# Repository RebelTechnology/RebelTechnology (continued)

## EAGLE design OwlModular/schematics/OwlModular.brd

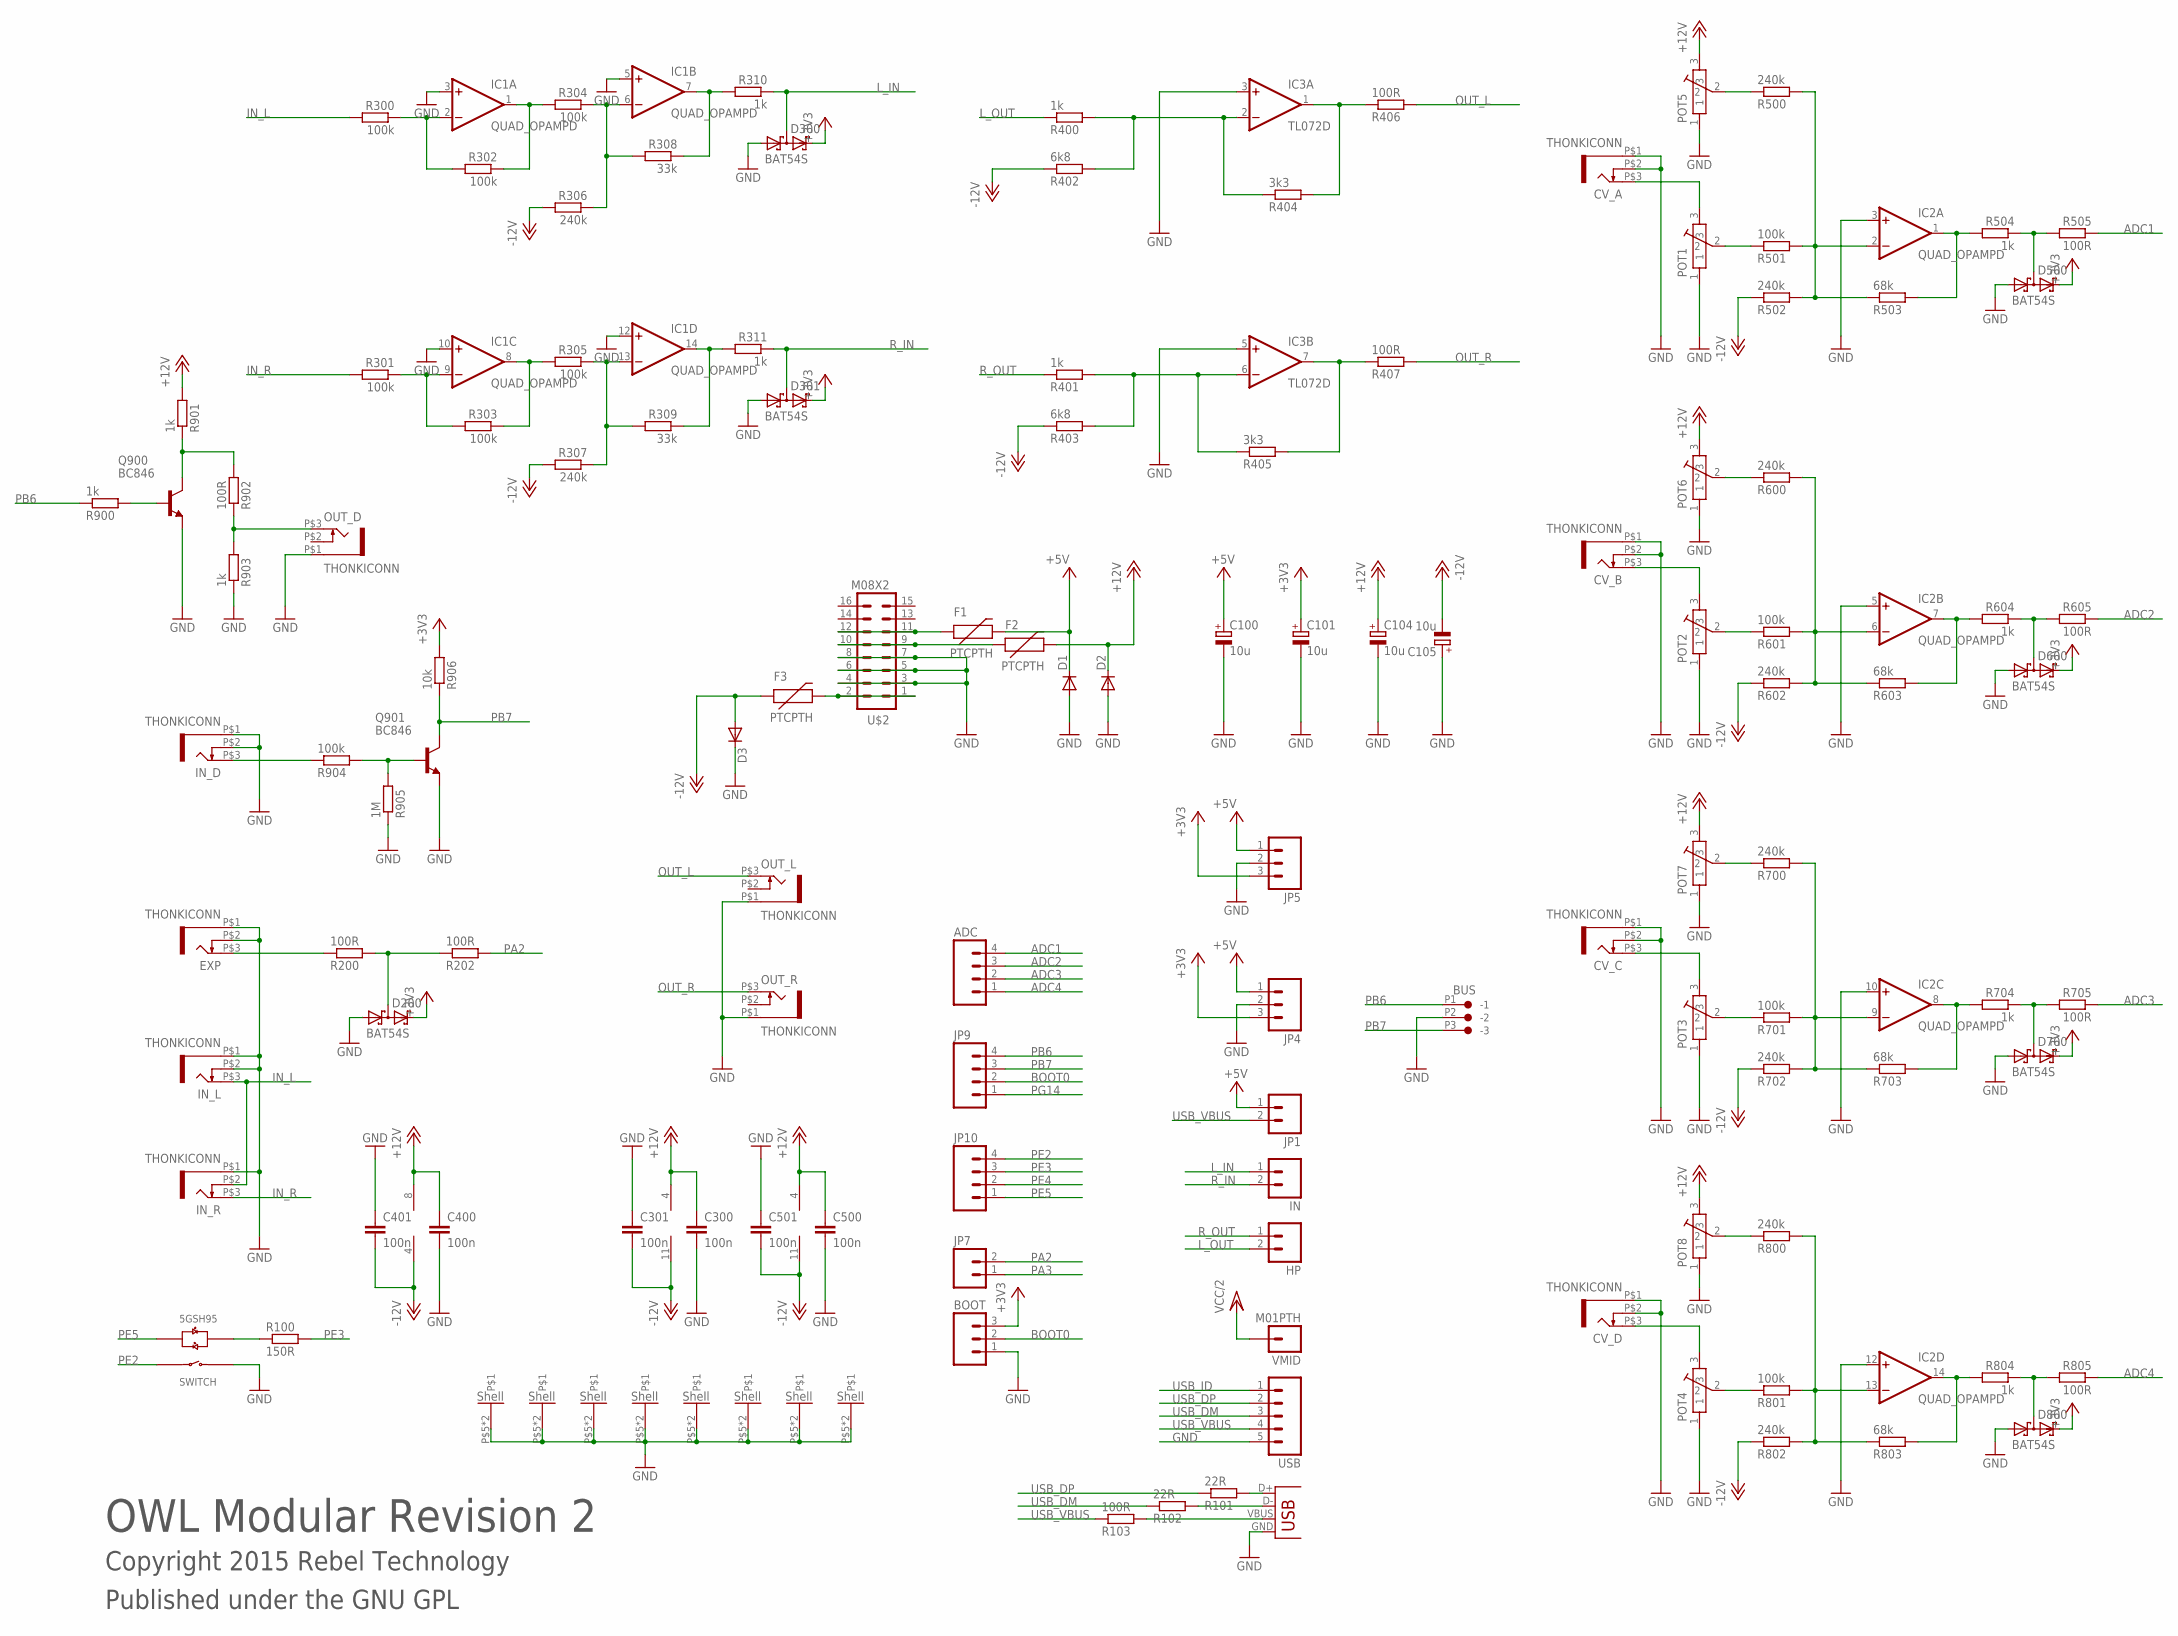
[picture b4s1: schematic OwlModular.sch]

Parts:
ADC: M04PTH; 1X04
BOOT: M03PTH; 1X03
BUS: CON-JST_PH_3W
C100, C101, C104, C105: 10u; PANASONIC_A
C300, C301, C400, C401, C500, C501: 100n; C0603
CV_A: THONKICONN
CV_B: THONKICONN
CV_C: THONKICONN
CV_D: THONKICONN
D1, D2, D3: DIODE1N4001; DIODE-1N4001
D200, D300, D301, D500, D600, D700, D800: BAT54S; SOT23
EXP: THONKICONN
F1, F2, F3: PTCPTH; PTC
HP: M02PTH; 1X02
IC1, IC2: QUAD_OPAMPD; SO14
IC3: TL072D; SO08
IN: M02PTH; 1X02
IN_D: THONKICONN
IN_L: THONKICONN
IN_R: THONKICONN
JP1, JP7: M02PTH; 1X02
JP4, JP5: M03PTH; 1X03
JP9, JP10: M04PTH; 1X04
OUT_D: THONKICONN
OUT_L: THONKICONN
OUT_R: THONKICONN
POT1, POT2, POT3, POT4, POT5, POT6, POT7, POT8: POT-ALPS-RK09L1140
Q900, Q901: BC846; SOT23
R100: 150R; 0603
R101, R102: 22R; 0603
R103, R200, R202, R406, R407, R505, R605, R705, R805, R902: 100R; 0603
R300, R301, R302, R303, R304, R305, R501, R601, R701, R801, R904: 100k; 0603
R306, R307, R500, R502, R600, R602, R700, R702, R800, R802: 240k; 0603
R308, R309: 33k; 0603
R310, R311, R400, R401, R504, R604, R704, R804, R900, R901, R903: 1k; 0603
R402, R403: 6k8; 0603
R404, R405: 3k3; 0603
R503, R603, R703, R803: 68k; 0603
R905: 1M; 0603
R906: 10k; 0603
U$1: 5GTH9
U$2: M08X2; 2X8
USB: M05PTH; 1X05
VMID: M01PTH; 1X01
X1: USBPTH-VERTICAL; USB-B-PTH-VERTICAL

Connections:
+3V3: BOOT.3, C101.+, D200.2 (C2), D300.2 (C2), D301.2 (C2), D500.2 (C2), D600.2 (C2), D700.2 (C2), D800.2 (C2), JP4.3, JP5.3, R906.2
+5V: C100.+, D1.C, F1.P$2 (2), JP1.1, JP4.1, JP5.1
+12V: C104.+, C300.1, C400.1, C500.1, D2.C, F2.P$2 (2), IC1.4 (V+), IC2.4 (V+), IC3.8 (V+), POT5.3, POT6.3, POT7.3, POT8.3, R901.2
-12V: C105.-, C301.2, C401.2, C501.2, D3.A, F3.P$1 (1), IC1.11 (V-), IC2.11 (V-), IC3.4 (V-), R306.2, R307.2, R402.1, R403.1, R502.1, R602.1, R702.1, R802.1
ADC1: ADC.4, R505.1
ADC2: ADC.3, R605.1
ADC3: ADC.2, R705.1
ADC4: ADC.1, R805.1
BOOT0: BOOT.2, JP9.2
GND: BOOT.1, BUS.P2 (-2), C100.-, C101.-, C104.-, C105.+, C300.2, C301.1, C400.2, C401.1, C500.2, C501.1, CV_A.P$1 (5), CV_A.P$2 (4), CV_B.P$1 (5), CV_B.P$2 (4), CV_C.P$1 (5), CV_C.P$2 (4), CV_D.P$1 (5), CV_D.P$2 (4), D1.A, D2.A, D3.C, D200.1 (A1), D300.1 (A1), D301.1 (A1), D500.1 (A1), D600.1 (A1), D700.1 (A1), D800.1 (A1), EXP.P$1 (5), EXP.P$2 (4), IC1.3 (+IN), IC1.5 (+IN), IC1.10 (+IN), IC1.12 (+IN), IC2.3 (+IN), IC2.5 (+IN), IC2.10 (+IN), IC2.12 (+IN), IC3.3 (+IN), IC3.5 (+IN), IN_D.P$1 (5), IN_D.P$2 (4), IN_L.P$1 (5), IN_L.P$2 (4), IN_R.P$1 (5), JP4.2, JP5.2, OUT_D.P$1 (5), OUT_L.P$1 (5), OUT_R.P$1 (5), POT1.1, POT1.P$5, POT1.P$6, POT2.1, POT2.P$5, POT2.P$6, POT3.1, POT3.P$5, POT3.P$6, POT4.1, POT4.P$5, POT4.P$6, POT5.1, POT5.P$5, POT5.P$6, POT6.1, POT6.P$5, POT6.P$6, POT7.1, POT7.P$5, POT7.P$6, POT8.1, POT8.P$5, POT8.P$6, Q900.2 (E), Q901.2 (E), R903.1, R905.1, U$1.1 (SWITCH_B), U$2.3, U$2.4, U$2.5, U$2.6, U$2.7, U$2.8, USB.5, X1.GND
IN_L: IN_L.P$3 (3), IN_R.P$2 (4), R300.2
IN_R: IN_R.P$3 (3), R301.2
L_IN: D300.3 (C1A2), IN.1, R310.1
L_OUT: HP.2, R400.1
unnamed: IC1.1 (OUT), R302.1, R304.2
unnamed: CV_A.P$3 (3), POT1.3
unnamed: POT1.2, R501.1
unnamed: IC1.8 (OUT), R303.1, R305.2
unnamed: IC1.9 (-IN), R301.1, R303.2
unnamed: F3.P$2 (2), U$2.1, U$2.2
unnamed: IC1.13 (-IN), R305.1, R307.1, R309.2
unnamed: IC1.2 (-IN), R300.1, R302.2
unnamed: R100.1, U$1.+3 (LED_R+)
unnamed: D200.3 (C1A2), R200.2, R202.1
unnamed: IC2.2 (-IN), R500.2, R501.2, R502.2, R503.1
unnamed: POT5.2, R500.1
unnamed: D500.3 (C1A2), R504.1, R505.2
unnamed: IC2.1 (OUT), R503.2, R504.2
unnamed: CV_B.P$3 (3), POT2.3
unnamed: POT2.2, R601.1
unnamed: IC2.6 (-IN), R600.2, R601.2, R602.2, R603.1
unnamed: POT6.2, R600.1
unnamed: IC2.7 (OUT), R603.2, R604.2
unnamed: D600.3 (C1A2), R604.1, R605.2
unnamed: CV_C.P$3 (3), POT3.3
unnamed: POT3.2, R701.1
unnamed: IC2.9 (-IN), R700.2, R701.2, R702.2, R703.1
unnamed: POT7.2, R700.1
unnamed: IC2.8 (OUT), R703.2, R704.2
unnamed: D700.3 (C1A2), R704.1, R705.2
unnamed: CV_D.P$3 (3), POT4.3
unnamed: POT4.2, R801.1
unnamed: IC1.6 (-IN), R304.1, R306.1, R308.2
unnamed: IC2.13 (-IN), R800.2, R801.2, R802.2, R803.1
unnamed: POT8.2, R800.1
unnamed: IC2.14 (OUT), R803.2, R804.2
unnamed: D800.3 (C1A2), R804.1, R805.2
unnamed: Q901.1 (B), R904.2, R905.2
unnamed: EXP.P$3 (3), R200.1
unnamed: IC3.1 (OUT), R404.2, R406.1
unnamed: IC3.7 (OUT), R405.2, R407.1
unnamed: IC3.2 (-IN), R400.2, R402.2, R404.1
unnamed: IC3.6 (-IN), R401.2, R403.2, R405.1
unnamed: F1.P$1 (1), U$2.11, U$2.12
unnamed: F2.P$1 (1), U$2.9, U$2.10
unnamed: IN_D.P$3 (3), R904.1
unnamed: Q900.3 (C), R901.1, R902.2
unnamed: OUT_D.P$3 (3), R902.1, R903.2
unnamed: Q900.1 (B), R900.2
unnamed: R101.2, X1.D+
unnamed: R102.2, X1.D-
unnamed: IC1.14 (OUT), R309.1, R311.2
unnamed: R103.2, X1.VBUS
unnamed: IC1.7 (OUT), R308.1, R310.2
OUT_L: OUT_L.P$3 (3), R406.2
OUT_R: OUT_R.P$3 (3), R407.2
PA2: JP7.2, R202.2
PA3: JP7.1
PB6: BUS.P1 (-1), JP9.4, R900.1
PB7: BUS.P3 (-3), JP9.3, Q901.3 (C), R906.1
PE2: JP10.4, U$1.4 (SWITCH_A)
PE3: JP10.3, R100.2
PE4: JP10.2
PE5: JP10.1, U$1.-2 (LED_G+)
PG14: JP9.1
R_IN: D301.3 (C1A2), IN.2, R311.1
R_OUT: HP.1, R401.1
USB_DM: R102.1, USB.3
USB_DP: R101.1, USB.2
USB_ID: USB.1
USB_VBUS: JP1.2, R103.1, USB.4
VCC/2: VMID.1

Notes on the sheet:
OWL Modular Revision 2
Copyright 2015 Rebel Technology
Published under the GNU GPL

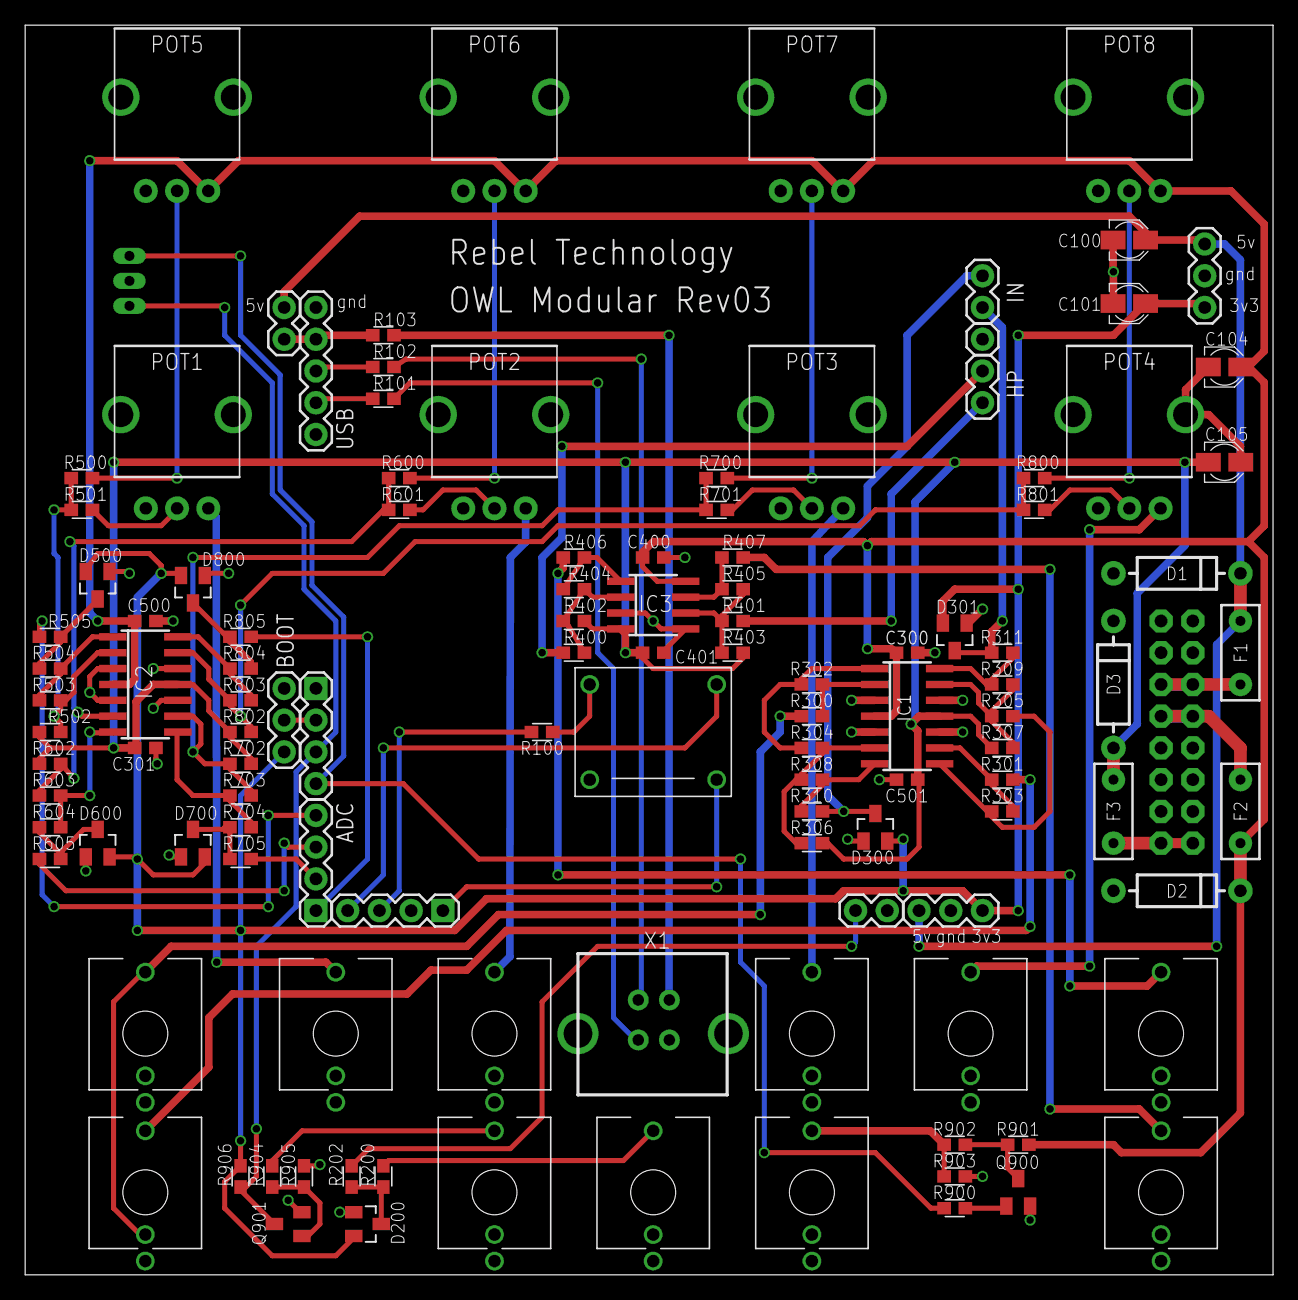
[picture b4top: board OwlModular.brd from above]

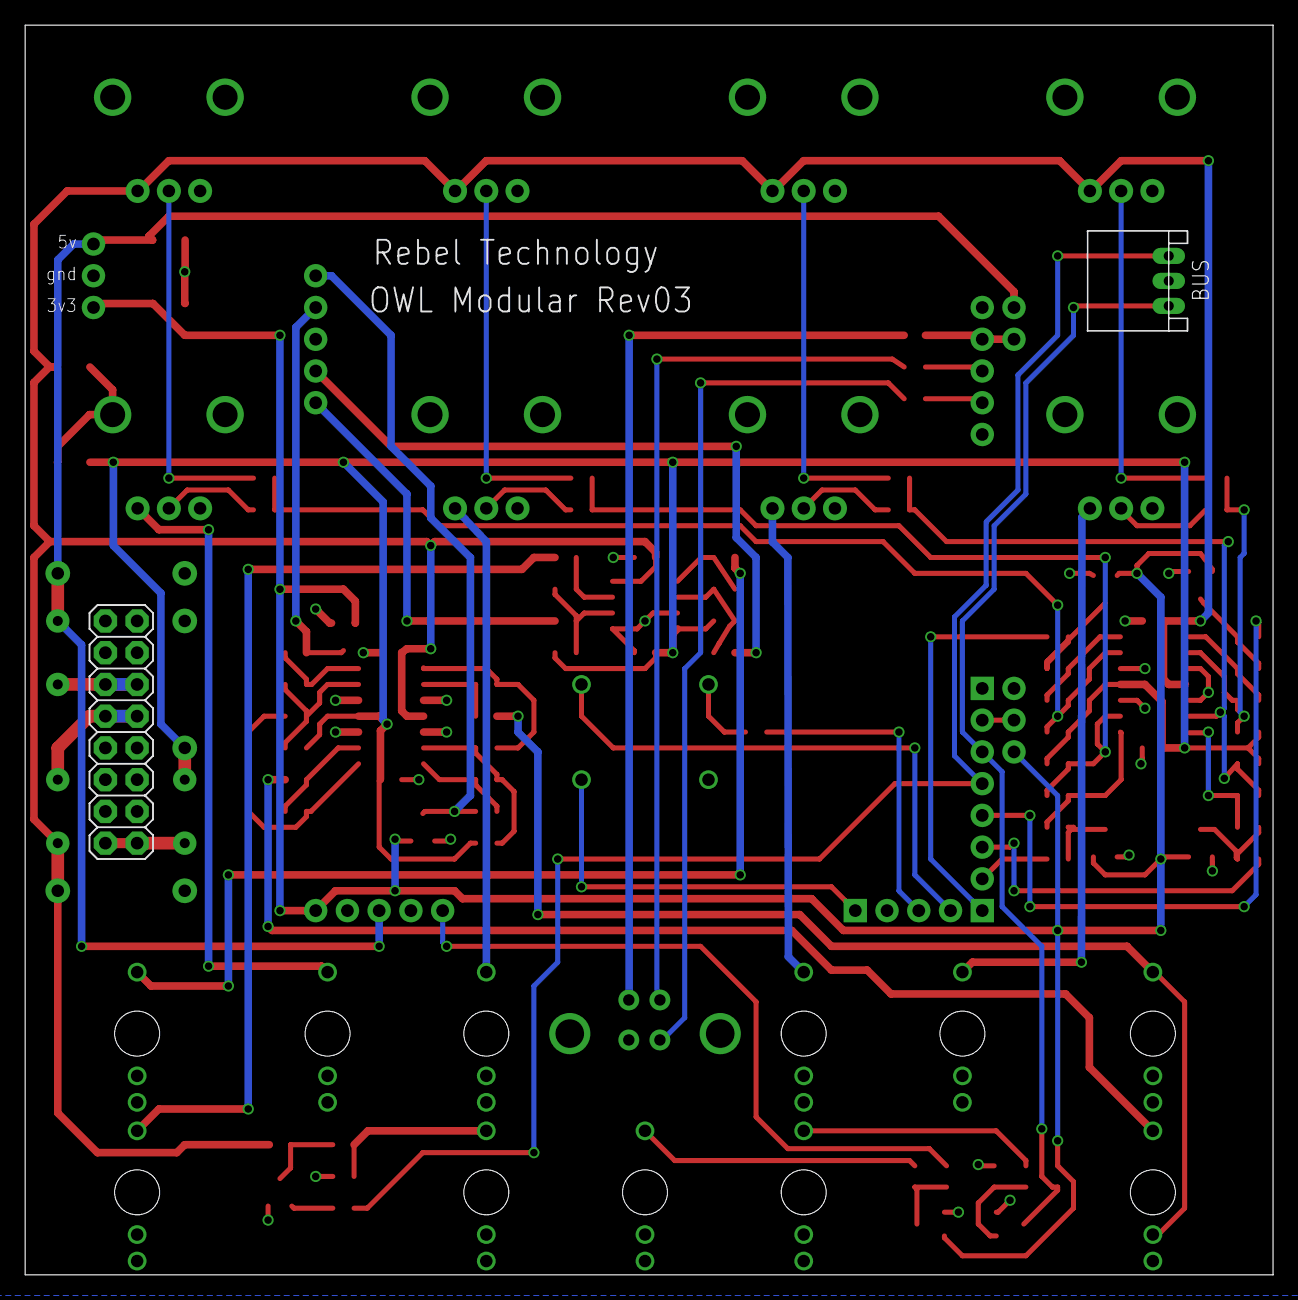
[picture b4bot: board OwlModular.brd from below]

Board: 2 copper layers, 99.9 x 100.0 mm, 120 parts (2 on the bottom side), 77 nets.

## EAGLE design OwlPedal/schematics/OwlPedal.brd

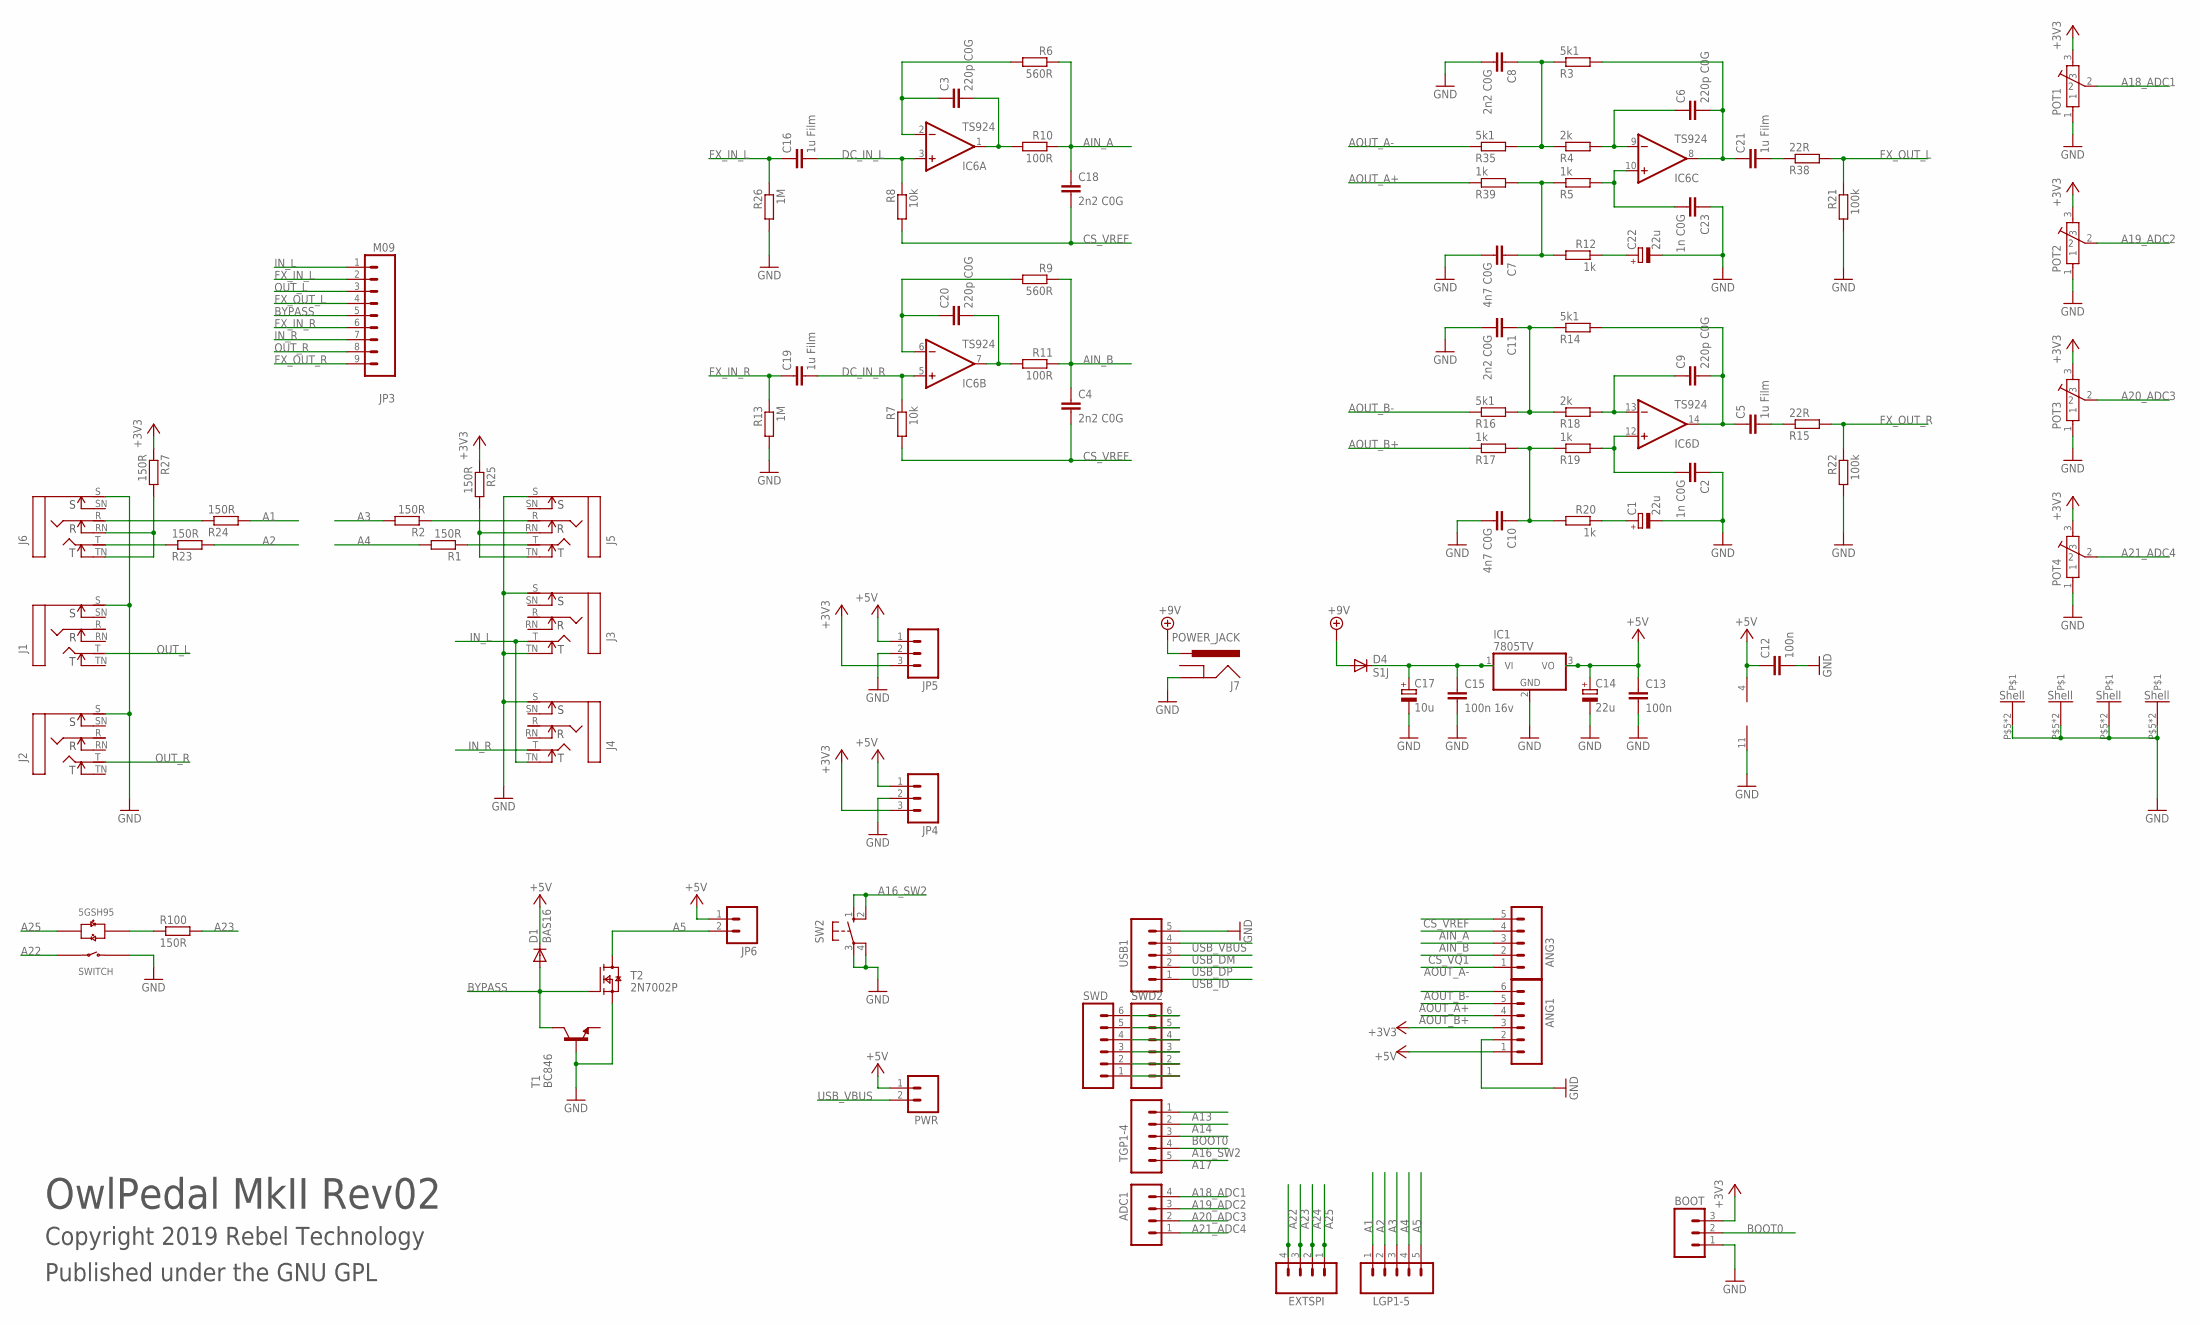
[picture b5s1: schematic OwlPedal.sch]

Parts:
ADC1: M04PTH; 1X04
ANG1: M06SIP; 1X06
ANG3: M05PTH; 1X05
BOOT: M03PTH; 1X03
C1, C14, C22: 22u; CPOL-5
C2, C23: 1n C0G; C0603
C3, C6, C9, C20: 220p C0G; C0603
C4, C8, C11, C18: 2n2 C0G; C0603
C5, C16, C19, C21: 1u Film; C1210
C7, C10: 4n7 C0G; C0603
C12, C13: 100n; C0603
C15: 100n 16v; C0603
C17: 10u; CPOL-5
D1: BAS16; SOT23
D4: S1J; SMA-DIODE
EXTSPI: M04PTH; 1X04
IC1: 7805TV; TO220V
IC6: TS924; SO14
J1, J2, J3, J4, J5, J6: NEUTRIK_NMJ6HCD2; NMJ6HCD2
J7: POWER_JACK; DC_JACK_SLOT
JP3: M09; 1X09
JP4, JP5: M03PTH; 1X03
JP6: M02PTH; 1X02
LGP1-5: M05PTH; 1X05
POT1, POT2, POT3, POT4: POT-ALPS-RK09L1140
PWR: M02PTH; 1X02
R1, R2, R23, R24, R25, R27, R100: 150R; 0603
R3, R14, R16, R35: 5k1; 0603
R4, R18: 2k; 0603
R5, R12, R17, R19, R20, R39: 1k; 0603
R6, R9: 560R; 0603
R7, R8: 10k; 0603
R10, R11: 100R; 0603
R13, R26: 1M; 0603
R15, R38: 22R; 0603
R21, R22: 100k; 0603
SW2: 10-XX; B3F-10XX
SWD, SWD2: M06SIP; 1X06
T1: BC846; SOT23
T2: 2N7002P; SOT23
TGP1-4: M05PTH; 1X05
U$1: 5GTH9
USB1: M05PTH; 1X05

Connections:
+3V3: ANG1.3, BOOT.3, JP4.3, JP5.3, POT1.3, POT2.3, POT3.3, POT4.3, R25.1, R27.1
+5V: ANG1.1, C12.1, C13.1, C14.+, D1.3 (K), IC1.3 (VO), IC6.4 (V+), JP4.1, JP5.1, JP6.1, PWR.1
+9V: D4.A, J7.PWR
A1: LGP1-5.1, R24.2
A2: LGP1-5.2, R23.2
A3: LGP1-5.3, R2.2
A4: LGP1-5.4, R1.2
A5: JP6.2, LGP1-5.5, T2.3 (D)
A13: TGP1-4.1
A14: TGP1-4.2
A16_SW2: SW2.1 (S), SW2.2 (S1), TGP1-4.4
A17: TGP1-4.5
A18_ADC1: ADC1.4, POT1.2
A19_ADC2: ADC1.3, POT2.2
A20_ADC3: ADC1.2, POT3.2
A21_ADC4: ADC1.1, POT4.2
A22: EXTSPI.4, U$1.4 (SWITCH_A)
A23: EXTSPI.3, R100.2
A24: EXTSPI.2
A25: EXTSPI.1, U$1.-2 (LED_G+)
AIN_A: ANG3.4, C18.1, R6.1, R10.1
AIN_B: ANG3.3, C4.1, R9.1, R11.1
AOUT_A+: ANG1.5, R39.1
AOUT_A-: ANG3.1, R35.1
AOUT_B+: ANG1.4, R17.1
AOUT_B-: ANG1.6, R16.1
BOOT0: BOOT.2, TGP1-4.3
BYPASS: D1.1 (A), JP3.5, T1.3 (C), T2.1 (G)
CS_VQ1: ANG3.2
CS_VREF: ANG3.5, C4.2, C18.2, R7.2, R8.2
DC_IN_L: C16.1, IC6.3 (+IN), R8.1
DC_IN_R: C19.1, IC6.5 (+IN), R7.1
FX_IN_L: C16.2, JP3.2, R26.1
FX_IN_R: C19.2, JP3.6, R13.1
FX_OUT_L: JP3.4, R21.1, R38.2
FX_OUT_R: JP3.9, R15.2, R22.1
GND: ANG1.2, BOOT.1, C1.-, C2.1, C7.2, C8.2, C10.2, C11.2, C12.2, C13.2, C14.-, C15.2, C17.-, C22.-, C23.1, IC1.2 (GND), IC6.11 (V-), J1.S, J2.S, J3.S, J3.TN, J4.S, J5.S, J6.S, J7.GND, JP4.2, JP5.2, POT1.1, POT1.P$5, POT1.P$6, POT2.1, POT2.P$5, POT2.P$6, POT3.1, POT3.P$5, POT3.P$6, POT4.1, POT4.P$5, POT4.P$6, R13.2, R21.2, R22.2, R26.2, SW2.3, SW2.4 (P1), T1.1 (B), T2.2 (S), U$1.1 (SWITCH_B), USB1.5
IN_L: J3.T, J4.TN, JP3.1
IN_R: J4.T, JP3.7
unnamed: J5.RN, J5.TN, R25.2
unnamed: J6.R, R24.1
unnamed: SWD.1, SWD2.1
unnamed: J6.RN, J6.TN, R27.2
unnamed: SWD.2, SWD2.2
unnamed: SWD.3, SWD2.3
unnamed: SWD.4, SWD2.4
unnamed: SWD.5, SWD2.5
unnamed: SWD.6, SWD2.6
unnamed: R100.1, U$1.+3 (LED_R+)
unnamed: C6.2, C21.1, IC6.8 (OUT), R3.2
unnamed: J5.R, R2.1
unnamed: C8.1, R3.1, R4.1, R35.2
unnamed: C20.1, IC6.6 (-IN), R9.2
unnamed: J5.T, R1.1
unnamed: C6.1, IC6.9 (-IN), R4.2
unnamed: C23.2, IC6.10 (+IN), R5.2
unnamed: C7.1, R5.1, R12.2, R39.2
unnamed: C9.1, IC6.13 (-IN), R18.2
unnamed: C2.2, IC6.12 (+IN), R19.2
unnamed: C10.1, R17.2, R19.1, R20.2
unnamed: C3.1, IC6.2 (-IN), R6.2
unnamed: C3.2, IC6.1 (OUT), R10.2
unnamed: C11.1, R14.1, R16.2, R18.1
unnamed: C20.2, IC6.7 (OUT), R11.2
unnamed: J6.T, R23.1
unnamed: C21.2, R38.1
unnamed: C22.+, R12.1
unnamed: C1.+, R20.1
unnamed: C5.1, C9.2, IC6.14 (OUT), R14.2
unnamed: C5.2, R15.1
unnamed: C15.1, C17.+, D4.C, IC1.1 (VI)
OUT_L: J1.T, JP3.3
OUT_R: J2.T, JP3.8
USB_DM: USB1.3
USB_DP: USB1.2
USB_ID: USB1.1
USB_VBUS: PWR.2, USB1.4

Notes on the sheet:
OwlPedal MkII Rev02
Copyright 2019 Rebel Technology
Published under the GNU GPL

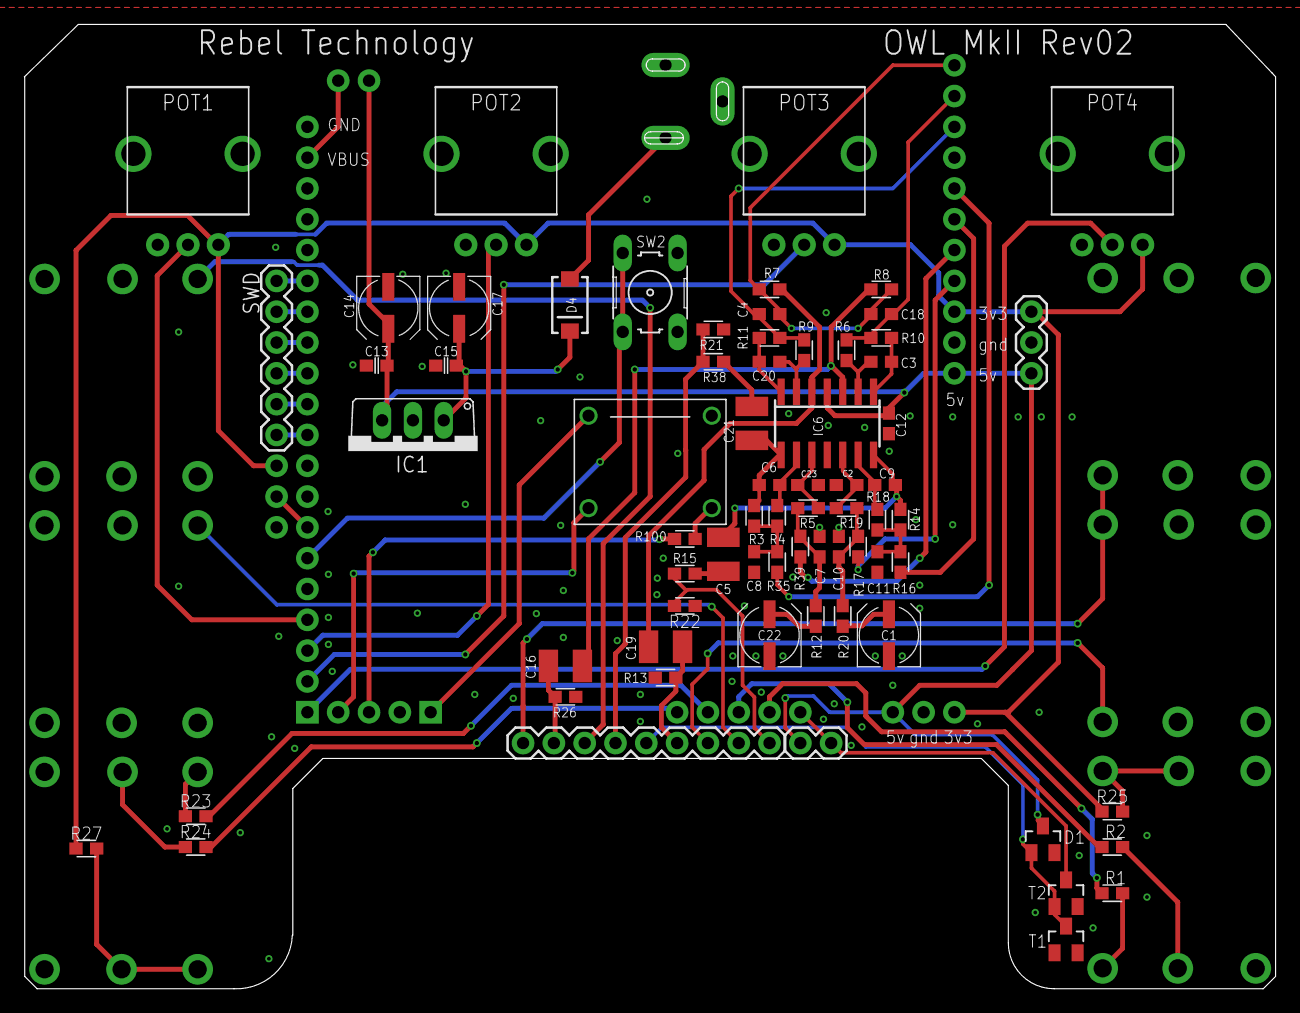
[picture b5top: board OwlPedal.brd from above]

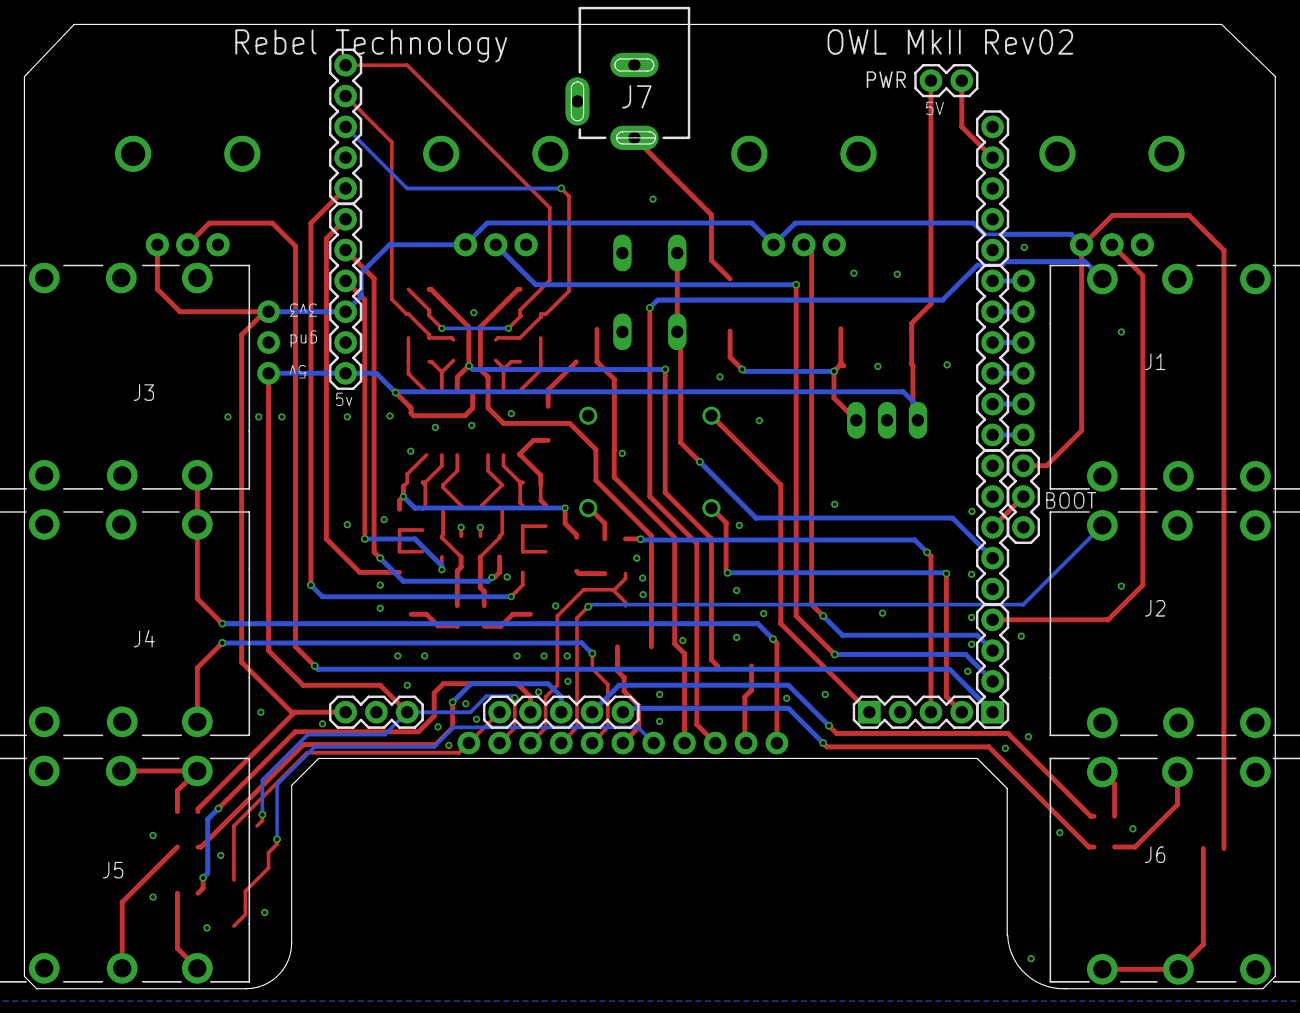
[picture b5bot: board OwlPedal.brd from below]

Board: 2 copper layers, 103.1 x 79.5 mm, 88 parts (18 on the bottom side), 69 nets.

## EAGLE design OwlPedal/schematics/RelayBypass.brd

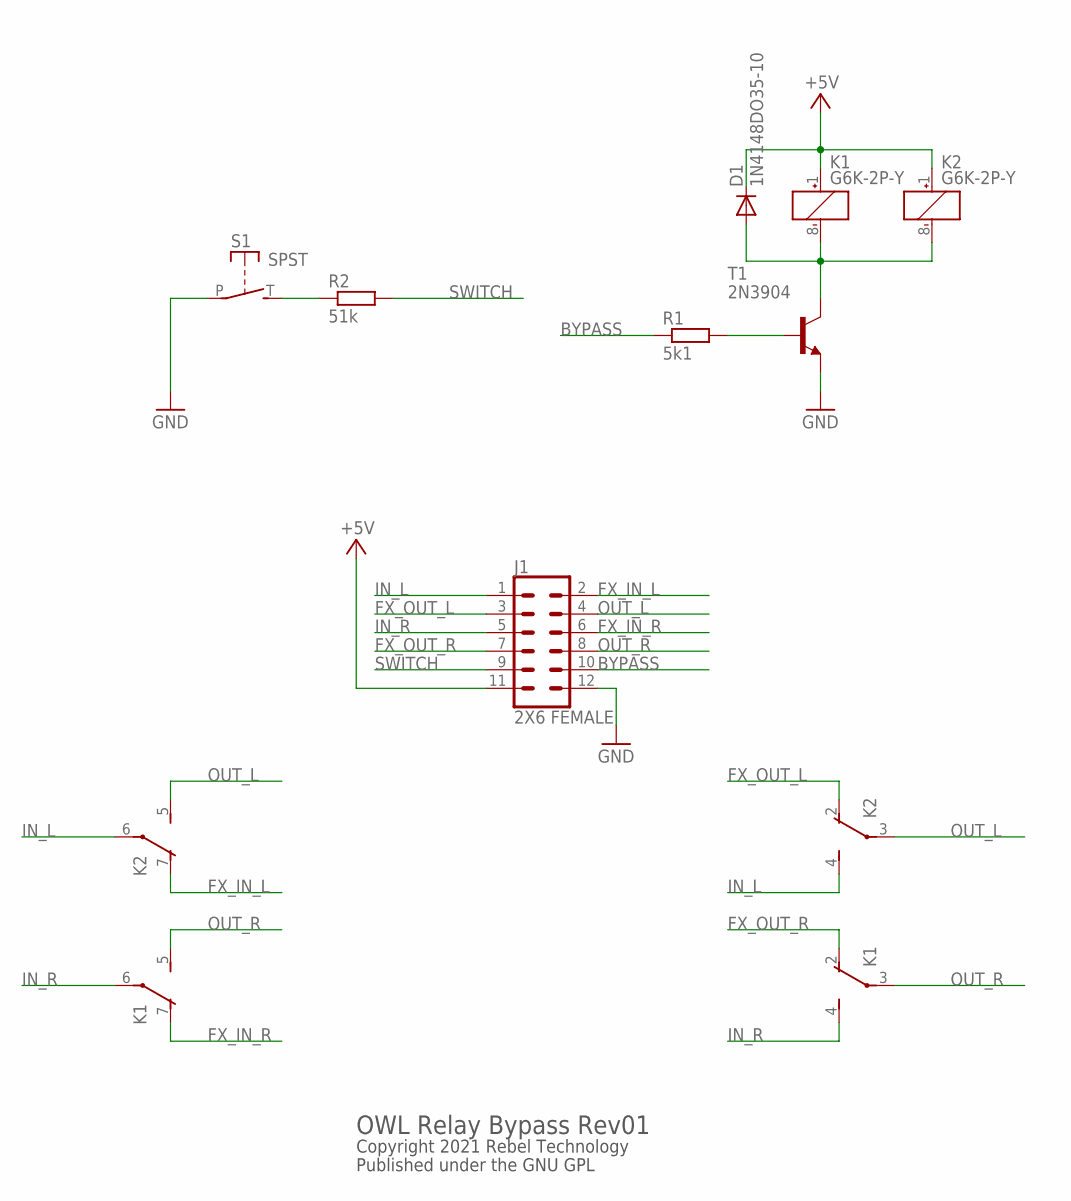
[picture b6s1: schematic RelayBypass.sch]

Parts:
D1: 1N4148DO35-10; DO35-10
J1: 2X6 FEMALE; 2X6
K1, K2: G6K-2P-Y
R1: 5k1; 0204/7
R2: 51k; 0204/7
S1: SPST; JUDCOSPST
T1: 2N3904; TO92

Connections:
+5V: D1.C, J1.11, K1.1 (+), K2.1 (+)
BYPASS: J1.10, R1.1
FX_IN_L: J1.2, K2.7 (O)
FX_IN_R: J1.6, K1.7 (O)
FX_OUT_L: J1.3, K2.2 (O)
FX_OUT_R: J1.7, K1.2 (O)
GND: J1.12, S1.P, T1.3 (E)
IN_L: J1.1, K2.4 (S), K2.6
IN_R: J1.5, K1.4 (S), K1.6
unnamed: R1.2, T1.2 (B)
unnamed: D1.A, K1.8 (-), K2.8 (-), T1.1 (C)
unnamed: R2.1, S1.T (S)
OUT_L: J1.4, K2.3, K2.5 (S)
OUT_R: J1.8, K1.3, K1.5 (S)
SWITCH: J1.9, R2.2

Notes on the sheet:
Copyright 2021 Rebel Technology
Published under the GNU GPL
OWL Relay Bypass Rev01

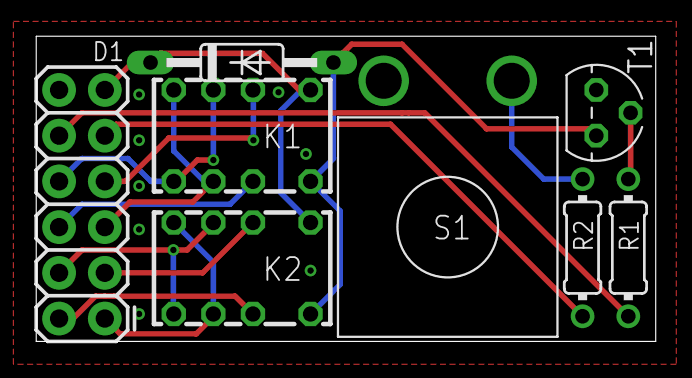
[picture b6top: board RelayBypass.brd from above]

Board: 2 copper layers, 34.4 x 17.0 mm, 8 parts (0 on the bottom side), 15 nets.
